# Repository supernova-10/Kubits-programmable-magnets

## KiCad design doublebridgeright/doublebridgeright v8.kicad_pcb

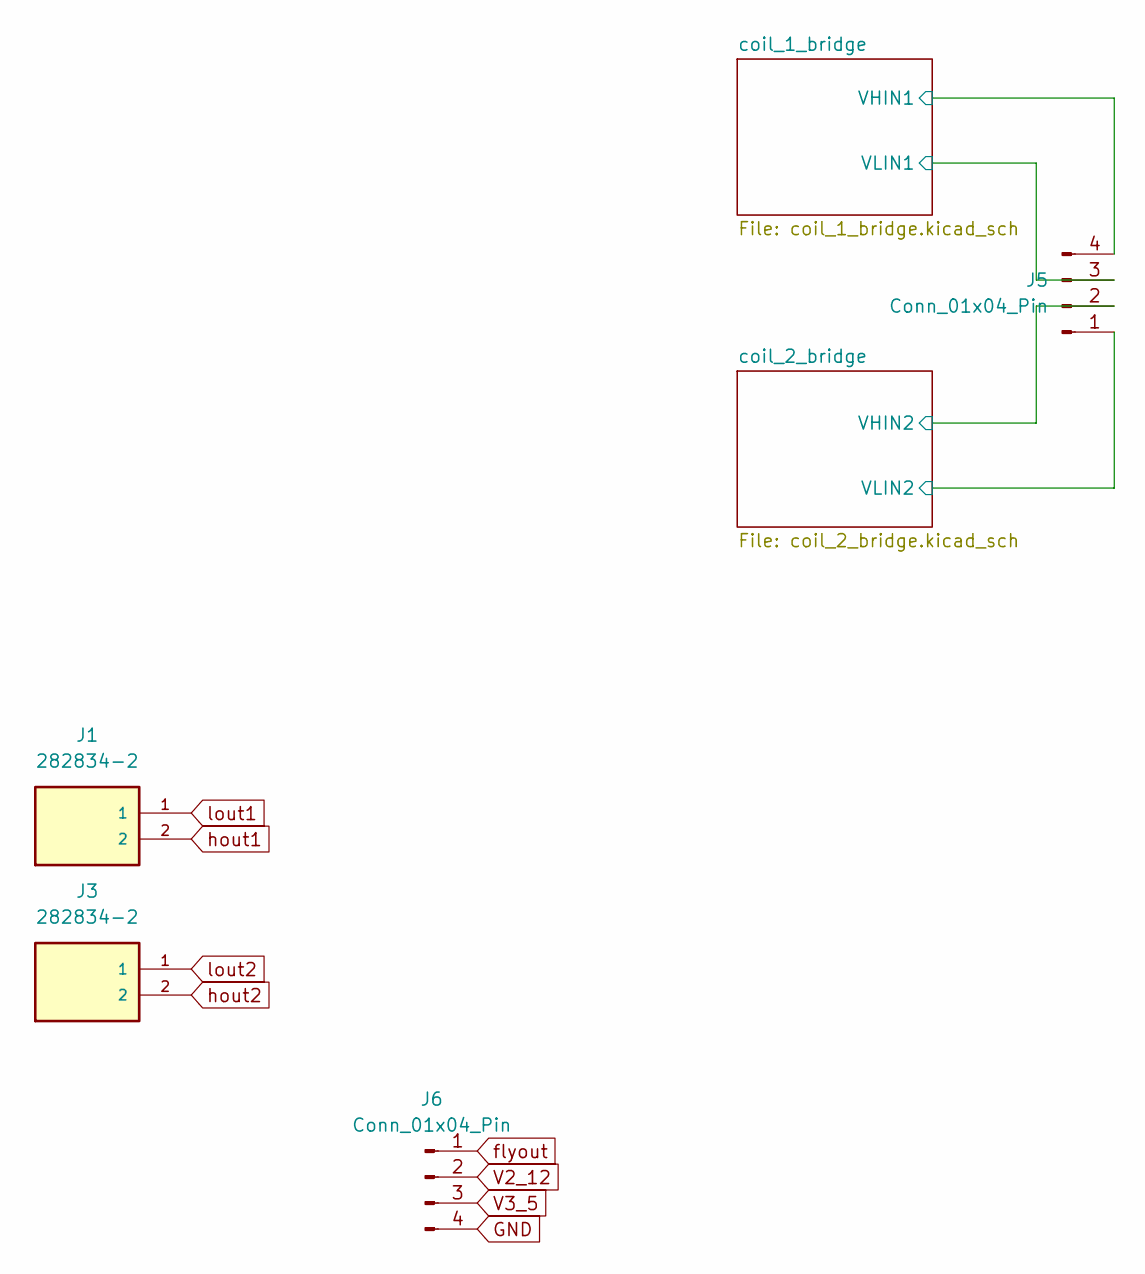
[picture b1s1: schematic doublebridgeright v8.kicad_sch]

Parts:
J1, J3: 282834-2; TE_282834-2; PARTREV D
J5, J6: Conn_01x04_Pin; PinHeader_1x04_P1.00mm_Horizontal

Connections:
/coil_1_bridge/VHIN1: J5.4; also elsewhere on the board
/coil_1_bridge/VLIN1: J5.3; also elsewhere on the board
/coil_2_bridge/VHIN2: J5.2; also elsewhere on the board
/coil_2_bridge/VLIN2: J5.1; also elsewhere on the board
GND: J6.4; also elsewhere on the board
V2_12: J6.2; also elsewhere on the board
V3_5: J6.3; also elsewhere on the board
flyout: J6.1; also elsewhere on the board
hout1: J1.2; also elsewhere on the board
hout2: J3.2; also elsewhere on the board
lout1: J1.1; also elsewhere on the board
lout2: J3.1; also elsewhere on the board

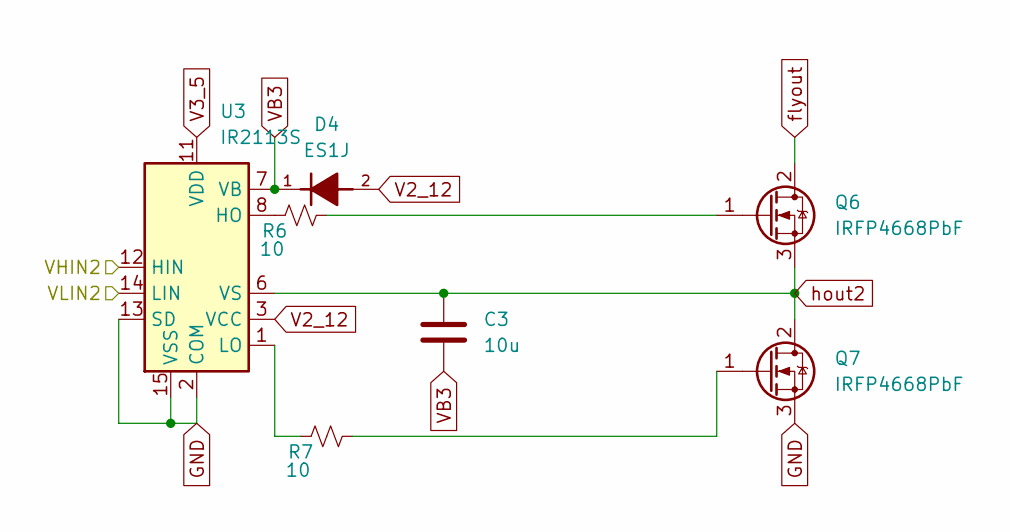
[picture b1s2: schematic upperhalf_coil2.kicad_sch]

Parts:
C3: 10u; C_1210_3225Metric
D4: ES1J; DIOM5227X250N; PARTREV Rev. 2
Q6, Q7: IRFP4668PbF; SC-59_Handsoldering
R6, R7: 10; R_0805_2012Metric
U3: IR2113S; SOIC-16W_7.5x10.3mm_P1.27mm

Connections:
/coil_2_bridge/VHIN2: U3.12 (HIN); also elsewhere on the board
/coil_2_bridge/VLIN2: U3.14 (LIN); also elsewhere on the board
GND: Q7.3 (S), U3.2 (COM), U3.13 (SD), U3.15 (VSS); also elsewhere on the board
unnamed: Q6.1 (G), R6.2
unnamed: Q7.1 (G), R7.2
unnamed: R6.1, U3.8 (HO)
unnamed: R7.1, U3.1 (LO)
V2_12: D4.2, U3.3 (VCC); also elsewhere on the board
V3_5: U3.11 (VDD); also elsewhere on the board
VB3: C3.2, D4.1, U3.7 (VB)
flyout: Q6.2 (D); also elsewhere on the board
hout2: C3.1, Q6.3 (S), Q7.2 (D), U3.6 (VS); also elsewhere on the board

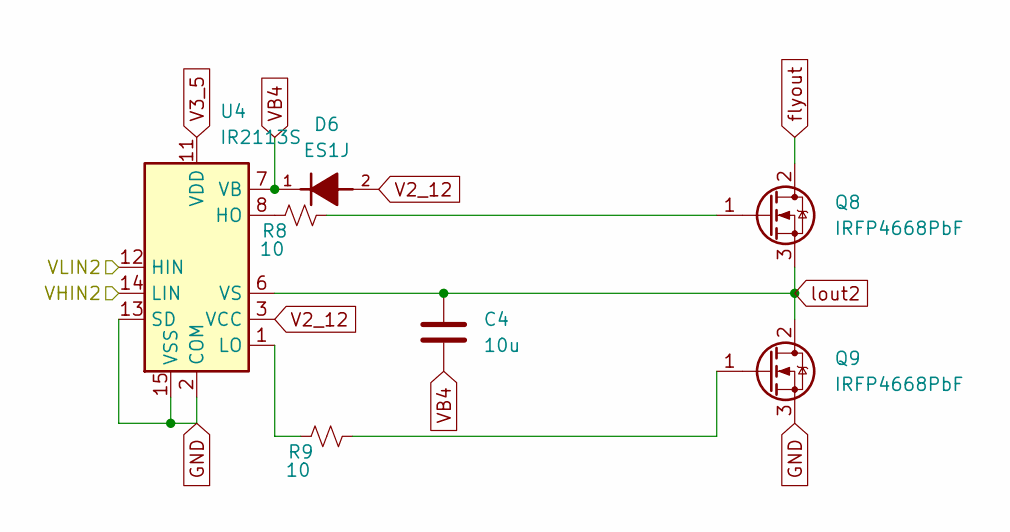
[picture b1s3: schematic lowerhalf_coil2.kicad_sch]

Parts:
C4: 10u; C_1210_3225Metric
D6: ES1J; DIOM5227X250N; PARTREV Rev. 2
Q8, Q9: IRFP4668PbF; SC-59_Handsoldering
R8, R9: 10; R_0805_2012Metric
U4: IR2113S; SOIC-16W_7.5x10.3mm_P1.27mm

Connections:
/coil_2_bridge/VHIN2: U4.14 (LIN); also elsewhere on the board
/coil_2_bridge/VLIN2: U4.12 (HIN); also elsewhere on the board
GND: Q9.3 (S), U4.2 (COM), U4.13 (SD), U4.15 (VSS); also elsewhere on the board
unnamed: Q8.1 (G), R8.2
unnamed: Q9.1 (G), R9.2
unnamed: R8.1, U4.8 (HO)
unnamed: R9.1, U4.1 (LO)
V2_12: D6.2, U4.3 (VCC); also elsewhere on the board
V3_5: U4.11 (VDD); also elsewhere on the board
VB4: C4.2, D6.1, U4.7 (VB)
flyout: Q8.2 (D); also elsewhere on the board
lout2: C4.1, Q8.3 (S), Q9.2 (D), U4.6 (VS); also elsewhere on the board

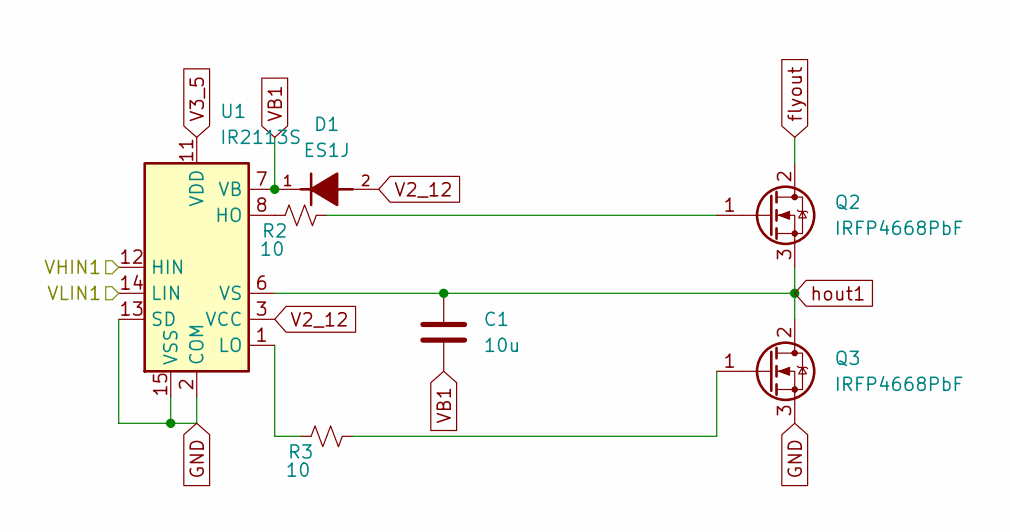
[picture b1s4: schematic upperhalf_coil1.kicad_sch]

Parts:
C1: 10u; C_1210_3225Metric
D1: ES1J; DIOM5227X250N; PARTREV Rev. 2
Q2, Q3: IRFP4668PbF; SC-59_Handsoldering
R2, R3: 10; R_0805_2012Metric
U1: IR2113S; SOIC-16W_7.5x10.3mm_P1.27mm

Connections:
/coil_1_bridge/VHIN1: U1.12 (HIN); also elsewhere on the board
/coil_1_bridge/VLIN1: U1.14 (LIN); also elsewhere on the board
GND: Q3.3 (S), U1.2 (COM), U1.13 (SD), U1.15 (VSS); also elsewhere on the board
unnamed: Q2.1 (G), R2.2
unnamed: Q3.1 (G), R3.2
unnamed: R2.1, U1.8 (HO)
unnamed: R3.1, U1.1 (LO)
V2_12: D1.2, U1.3 (VCC); also elsewhere on the board
V3_5: U1.11 (VDD); also elsewhere on the board
VB1: C1.2, D1.1, U1.7 (VB)
flyout: Q2.2 (D); also elsewhere on the board
hout1: C1.1, Q2.3 (S), Q3.2 (D), U1.6 (VS); also elsewhere on the board

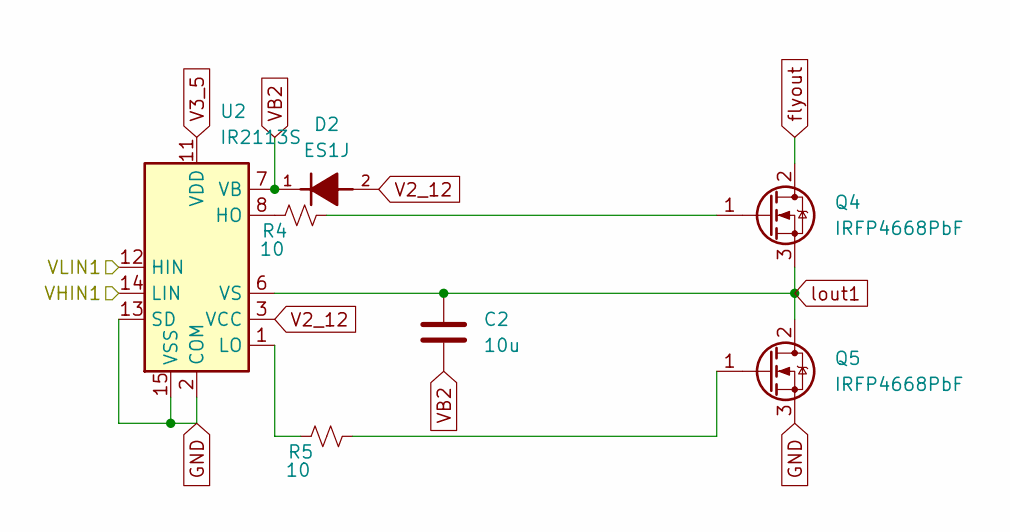
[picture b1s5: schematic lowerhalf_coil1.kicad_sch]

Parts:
C2: 10u; C_1210_3225Metric
D2: ES1J; DIOM5227X250N; PARTREV Rev. 2
Q4, Q5: IRFP4668PbF; SC-59_Handsoldering
R4, R5: 10; R_0805_2012Metric
U2: IR2113S; SOIC-16W_7.5x10.3mm_P1.27mm

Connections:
/coil_1_bridge/VHIN1: U2.14 (LIN); also elsewhere on the board
/coil_1_bridge/VLIN1: U2.12 (HIN); also elsewhere on the board
GND: Q5.3 (S), U2.2 (COM), U2.13 (SD), U2.15 (VSS); also elsewhere on the board
unnamed: Q4.1 (G), R4.2
unnamed: Q5.1 (G), R5.2
unnamed: R4.1, U2.8 (HO)
unnamed: R5.1, U2.1 (LO)
V2_12: D2.2, U2.3 (VCC); also elsewhere on the board
V3_5: U2.11 (VDD); also elsewhere on the board
VB2: C2.2, D2.1, U2.7 (VB)
flyout: Q4.2 (D); also elsewhere on the board
lout1: C2.1, Q4.3 (S), Q5.2 (D), U2.6 (VS); also elsewhere on the board

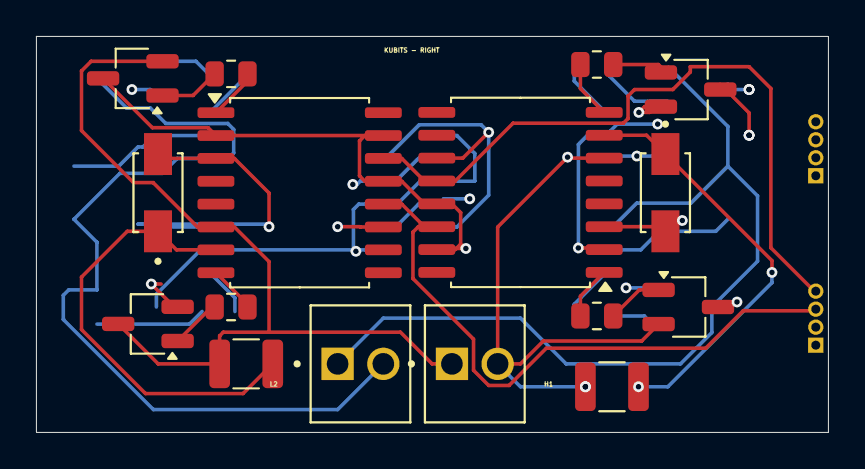
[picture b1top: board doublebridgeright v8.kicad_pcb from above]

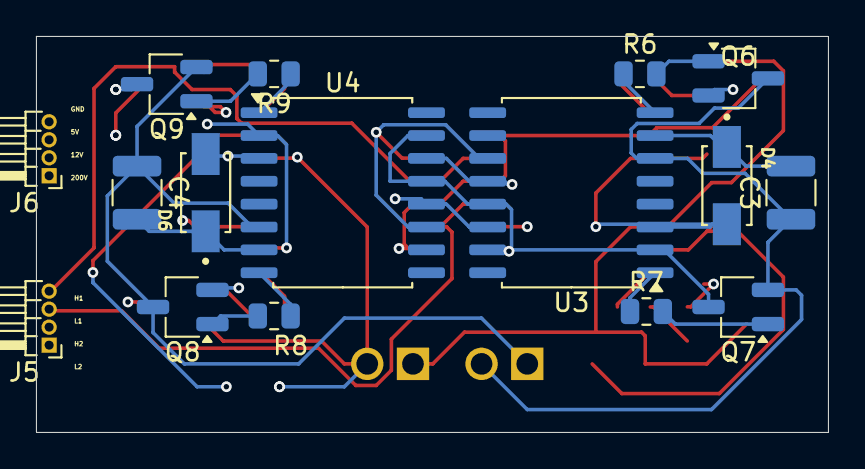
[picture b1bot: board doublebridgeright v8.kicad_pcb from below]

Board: 4 copper layers, 44.0 x 22.0 mm, 32 parts (16 on the bottom side), 32 nets.

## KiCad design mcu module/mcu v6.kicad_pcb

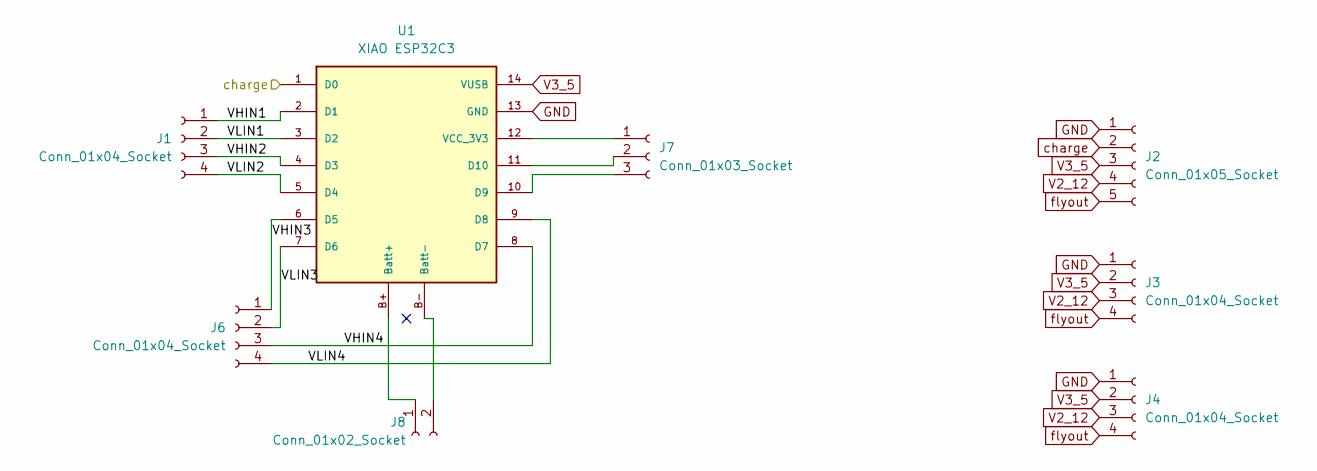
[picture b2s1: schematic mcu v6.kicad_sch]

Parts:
J1, J3, J4, J6: Conn_01x04_Socket; PinSocket_1x04_P1.00mm_Vertical
J2: Conn_01x05_Socket; PinSocket_1x05_P1.00mm_Vertical
J7: Conn_01x03_Socket; PinSocket_1x03_P1.00mm_Vertical
J8: Conn_01x02_Socket; PinSocket_1x02_P1.00mm_Vertical
U1: XIAO ESP32C3; xiao_esp32c3

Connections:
/VHIN1: J1.1, U1.2 (D1)
/VHIN2: J1.3, U1.4 (D3)
/VHIN3: J6.1, U1.6 (D5)
/VHIN4: J6.3, U1.8 (D7)
/VLIN1: J1.2, U1.3 (D2)
/VLIN2: J1.4, U1.5 (D4)
/VLIN3: J6.2, U1.7 (D6)
/VLIN4: J6.4, U1.9 (D8)
GND: J2.1, J3.1, J4.1, U1.13 (GND)
unnamed: J7.1, U1.12 (VCC_3V3)
unnamed: J7.2, U1.11 (D10)
unnamed: J7.3, U1.10 (D9)
unnamed: J8.1, U1.B+ (Batt+)
unnamed: J8.2, U1.B- (Batt-)
V2_12: J2.4, J3.3, J4.3
V3_5: J2.3, J3.2, J4.2, U1.14 (VUSB)
charge: J2.2, U1.1 (D0)
flyout: J2.5, J3.4, J4.4

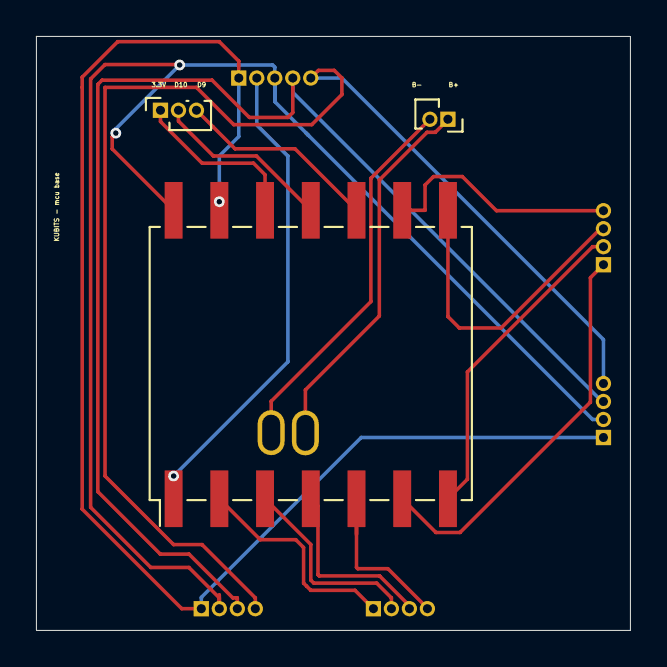
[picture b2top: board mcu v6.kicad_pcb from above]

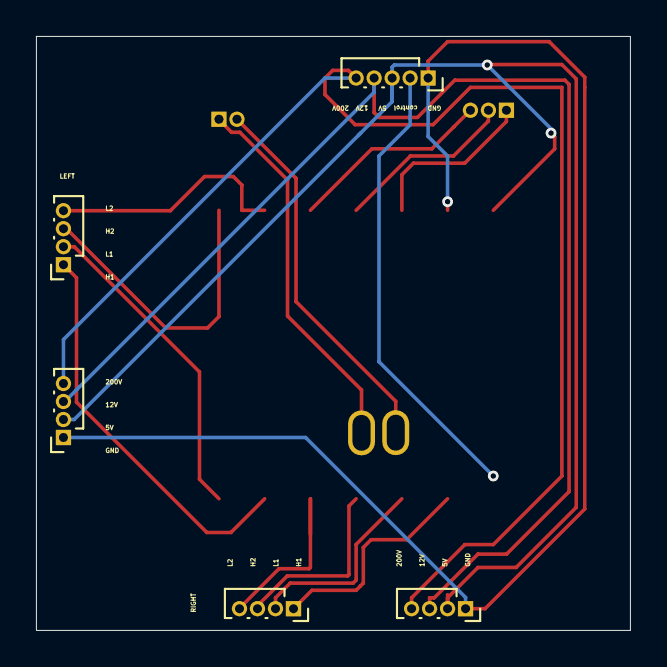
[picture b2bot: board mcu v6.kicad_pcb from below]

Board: 2 copper layers, 33.0 x 33.0 mm, 8 parts (5 on the bottom side), 18 nets.

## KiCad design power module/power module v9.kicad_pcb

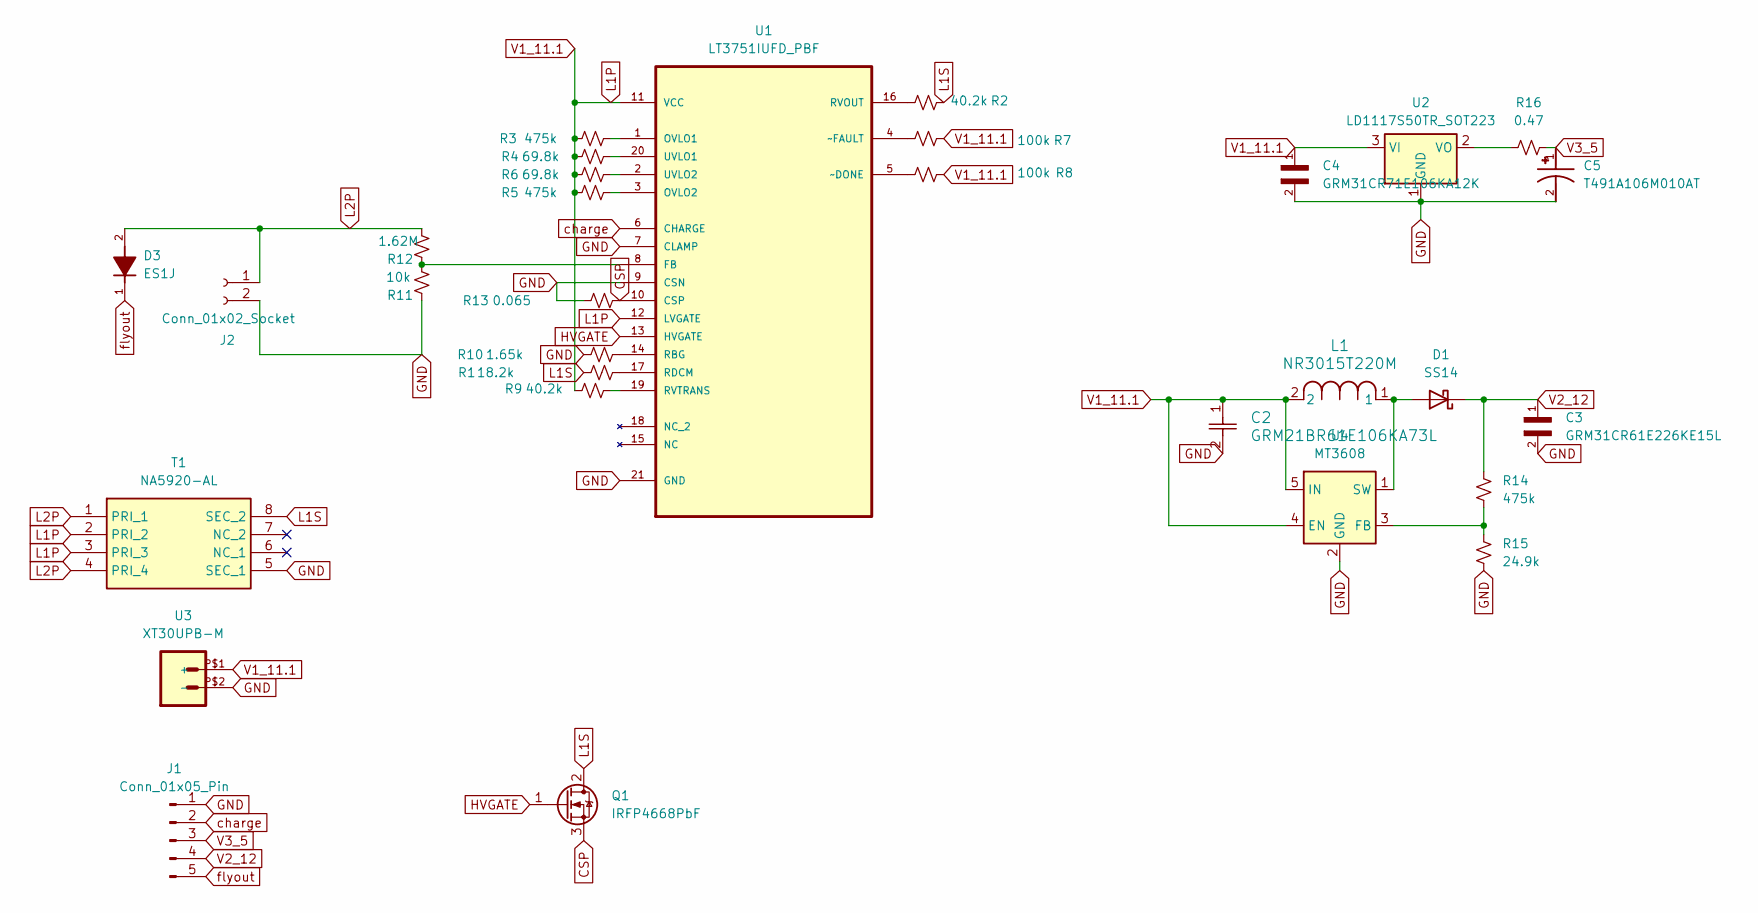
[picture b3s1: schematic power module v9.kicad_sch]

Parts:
C2: GRM21BR61E106KA73L; G-21_MUR
C3: GRM31CR61E226KE15L; CAPC3216X125N
C4: GRM31CR71E106KA12K; CAPC3216X180N
C5: T491A106M010AT; CAPPM3216X180N; PARTREV None
D1: SS14; D_SMA
D3: ES1J; DIOM5227X250N; PARTREV Rev. 2
J1: Conn_01x05_Pin; PinHeader_1x05_P1.00mm_Horizontal
J2: Conn_01x02_Socket; PinSocket_1x02_P1.00mm_Vertical
L1: NR3015T220M; IND_TAIYO_NR3015_TAY
Q1: IRFP4668PbF; SC-59_Handsoldering
R1: 18.2k; R_01005_0402Metric
R2, R9: 40.2k; R_01005_0402Metric
R3, R5: 475k; R_01005_0402Metric
R4, R6: 69.8k; R_01005_0402Metric
R7, R8: 100k; R_01005_0402Metric
R10: 1.65k; R_01005_0402Metric
R11: 10k; R_01005_0402Metric
R12: 1.62M; R_01005_0402Metric
R13: 0.065; R_01005_0402Metric
R14: 475k; R_0402_1005Metric
R15: 24.9k; R_0402_1005Metric
R16: 0.47; R_0402_1005Metric
T1: NA5920-AL; NA5920ALD; Manufacturer_Part_Number NA5920-AL; Mouser Part Number 994-NA5920-ALD
U1: LT3751IUFD_PBF; QFN-20_UFD_LIT-M; MPN LT3751IUFD#PBF
U2: LD1117S50TR_SOT223; SOT-223-3_TabPin2
U3: XT30UPB-M
U4: MT3608; SOT-23-6

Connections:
CSP: Q1.3 (S), R13.2, U1.10 (CSP)
GND: C2.2, C3.2, C4.2, C5.2, J1.1, J2.2, R10.1, R11.1, R13.1, R15.2, T1.5 (SEC_1), U1.7 (CLAMP), U1.9 (CSN), U1.21 (GND), U2.1 (GND), U3.P$2 (-), U4.2 (GND)
HVGATE: Q1.1 (G), U1.13 (HVGATE)
L1P: C2.1, C4.1, L1.2, R3.1, R4.1, R5.1, R6.1, R7.2, R8.2, R9.1, T1.2 (PRI_2), T1.3 (PRI_3), U1.11 (VCC), U1.12 (LVGATE), U2.3 (VI), U3.P$1 (+), U4.4 (EN), U4.5 (IN)
L1S: Q1.2 (D), R1.1, R2.2, T1.8 (SEC_2)
L2P: D3.2, J2.1, R12.2, T1.1 (PRI_1), T1.4 (PRI_4)
unnamed: D1.2 (A), L1.1, U4.1 (SW)
unnamed: R11.2, R12.1, U1.8 (FB)
unnamed: R3.2, U1.1 (OVLO1)
unnamed: R5.2, U1.3 (OVLO2)
unnamed: R10.2, U1.14 (RBG)
unnamed: R1.2, U1.17 (RDCM)
unnamed: R2.1, U1.16 (RVOUT)
unnamed: R9.2, U1.19 (RVTRANS)
unnamed: R4.2, U1.20 (UVLO1)
unnamed: R6.2, U1.2 (UVLO2)
unnamed: R8.1, U1.5 (~DONE)
unnamed: R7.1, U1.4 (~FAULT)
unnamed: R16.2, U2.2 (VO)
unnamed: R14.2, R15.1, U4.3 (FB)
V2_12: C3.1, D1.1 (K), J1.4, R14.1
V3_5: C5.1, J1.3, R16.1
charge: J1.2, U1.6 (CHARGE)
flyout: D3.1, J1.5

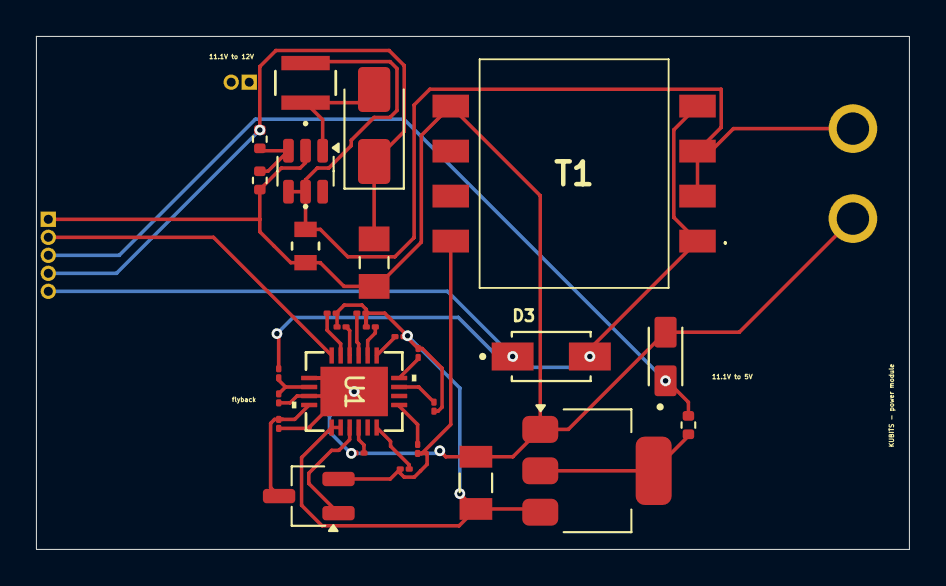
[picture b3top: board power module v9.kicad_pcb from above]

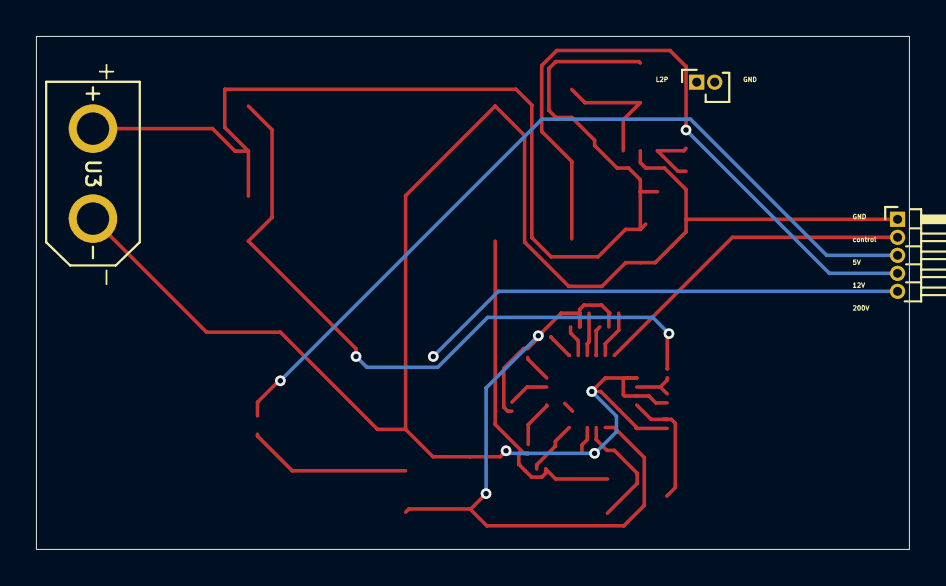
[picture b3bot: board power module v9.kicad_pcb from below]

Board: 2 copper layers, 48.5 x 28.5 mm, 31 parts (3 on the bottom side), 24 nets.

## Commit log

2025-09-04 Create PCB files
